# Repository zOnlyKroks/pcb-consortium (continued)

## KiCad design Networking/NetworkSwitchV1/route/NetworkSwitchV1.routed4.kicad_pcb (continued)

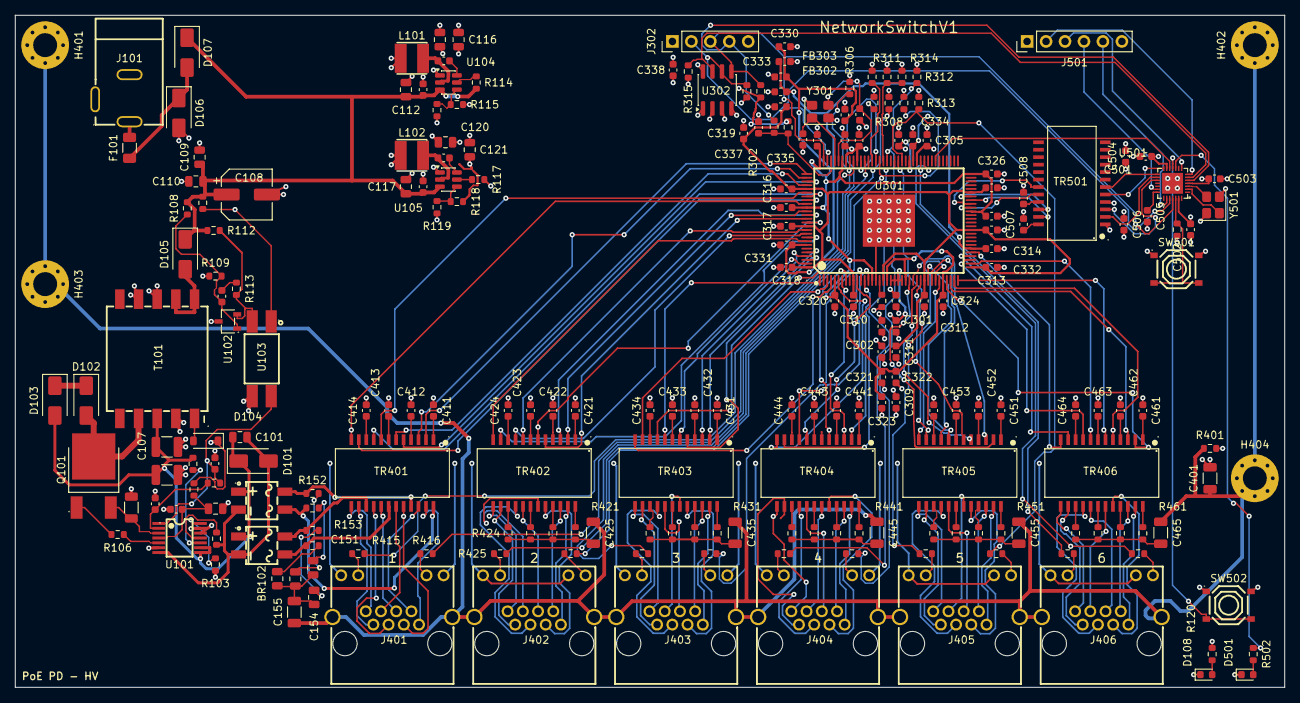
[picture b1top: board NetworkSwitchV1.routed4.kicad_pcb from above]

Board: 4 copper layers, 170.0 x 90.0 mm, 226 parts (0 on the bottom side), 251 nets.

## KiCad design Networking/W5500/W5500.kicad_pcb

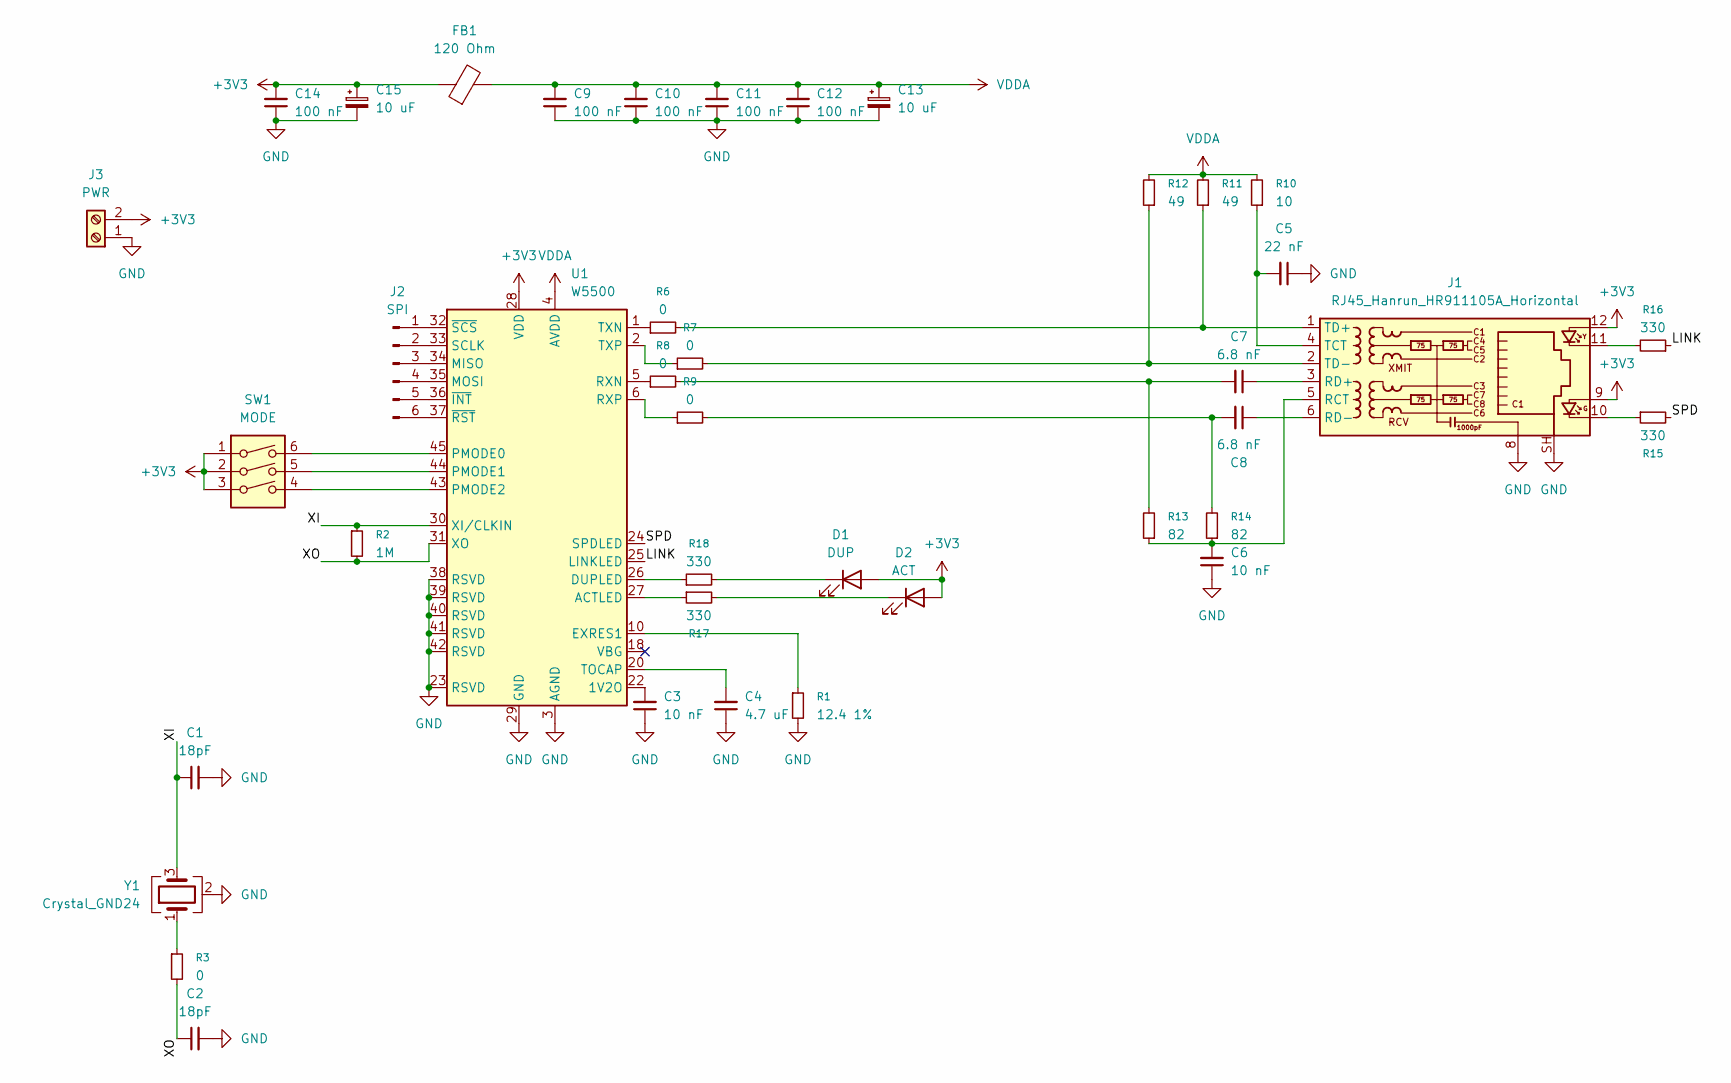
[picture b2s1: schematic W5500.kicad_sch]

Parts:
C1, C2: 18pF; C_0603_1608Metric
C3, C6: 10 nF; C_0603_1608Metric
C4: 4.7 uF; C_0805_2012Metric
C5: 22 nF; C_0603_1608Metric
C7, C8: 6.8 nF; C_0603_1608Metric
C9, C10, C11, C12, C14: 100 nF; C_0603_1608Metric
C13, C15: 10 uF; C_0805_2012Metric
D1: DUP; LED_0603_1608Metric
D2: ACT; LED_0603_1608Metric
FB1: 120 Ohm; R_0603_1608Metric
J1: RJ45_Hanrun_HR911105A_Horizontal
J2: SPI; PinHeader_1x06_P2.54mm_Vertical
J3: PWR; WJ500V-5.08-2P
R1: 12.4 1%; R_0603_1608Metric
R2: 1M; R_0603_1608Metric
R3, R6, R7, R8, R9: 0; R_0603_1608Metric
R10: 10; R_0603_1608Metric
R11, R12: 49; R_0603_1608Metric
R13, R14: 82; R_0603_1608Metric
R15, R16, R17, R18: 330; R_0603_1608Metric
SW1: MODE
U1: W5500; LQFP-48_7x7mm_P0.5mm
Y1: Crystal_GND24; Crystal_SMD_3225-4Pin_3.2x2.5mm

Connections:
+3V3: C14.2, C15.1, D1.2 (A), D2.2 (A), FB1.1, J1.9, J1.12, J3.2, SW1.1, SW1.2, SW1.3, U1.28 (VDD)
/LINK: R16.1, U1.25 (LINKLED)
/SPD: R15.2, U1.24 (SPDLED)
/XI: C1.1, R2.1, U1.30 (XI/CLKIN), Y1.3
/XO: C2.1, R2.2, R3.2, U1.31 (XO)
GND: C1.2, C2.2, C3.1, C4.1, C5.1, C6.1, C9.1, C10.1, C11.1, C12.1, C13.2, C14.1, C15.2, J1.8, J1.SH, J3.1, R1.2, U1.3 (AGND), U1.9 (AGND), U1.14 (AGND), U1.16 (AGND), U1.19 (AGND), U1.23 (RSVD), U1.29 (GND), U1.38 (RSVD), U1.39 (RSVD), U1.40 (RSVD), U1.41 (RSVD), U1.42 (RSVD), U1.48 (AGND), Y1.2 (G), Y1.4 (G)
unnamed: C7.2, R8.2, R13.2
unnamed: C8.2, R9.2, R14.2
unnamed: D1.1 (K), R18.2
unnamed: D2.1 (K), R17.2
unnamed: J1.10, R15.1
unnamed: J1.11, R16.2
unnamed: C6.2, J1.5 (RCT), R13.1, R14.1
unnamed: C7.1, J1.3 (RD+)
unnamed: C8.1, J1.6 (RD-)
unnamed: C5.2, J1.4 (TCT), R10.1
unnamed: J1.1 (TD+), R6.2, R11.1
unnamed: J1.2 (TD-), R7.2, R12.1
unnamed: J2.1, U1.32 (~SCS)
unnamed: J2.2, U1.33 (SCLK)
unnamed: J2.3, U1.34 (MISO)
unnamed: J2.4, U1.35 (MOSI)
unnamed: J2.5, U1.36 (~INT)
unnamed: J2.6, U1.37 (~RST)
unnamed: R3.1, Y1.1
unnamed: C3.2, U1.22 (1V2O)
unnamed: R17.1, U1.27 (ACTLED)
unnamed: R18.1, U1.26 (DUPLED)
unnamed: R1.1, U1.10 (EXRES1)
unnamed: SW1.6, U1.45 (PMODE0)
unnamed: SW1.5, U1.44 (PMODE1)
unnamed: SW1.4, U1.43 (PMODE2)
unnamed: R8.1, U1.5 (RXN)
unnamed: R9.1, U1.6 (RXP)
unnamed: C4.2, U1.20 (TOCAP)
unnamed: R6.1, U1.1 (TXN)
unnamed: R7.1, U1.2 (TXP)
VDDA: C9.2, C10.2, C11.2, C12.2, C13.1, FB1.2, R10.2, R11.2, R12.2, U1.4 (AVDD), U1.8 (AVDD), U1.11 (AVDD), U1.15 (AVDD), U1.17 (AVDD), U1.21 (AVDD)

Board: 2 copper layers, 39 parts (0 on the bottom side), 35 nets, no tracks yet.

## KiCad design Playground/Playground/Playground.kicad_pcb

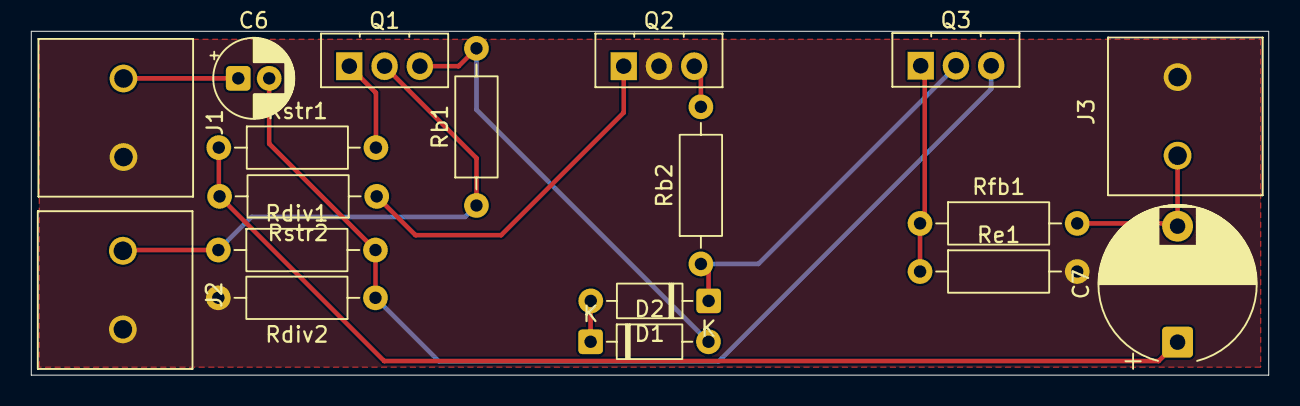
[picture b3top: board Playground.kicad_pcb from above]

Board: 2 copper layers, 80.0 x 22.2 mm, 18 parts (0 on the bottom side), 13 nets.

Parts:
C6: 1 uF; CP_Radial_D5.0mm_P2.00mm
C7: 1000 uF; CP_Radial_D10.0mm_P7.50mm
D1, D2: 1N4148; D_DO-35_SOD27_P7.62mm_Horizontal
J1, J2: Vin; WJ500V-5.08-2P
J3: Out; WJ500V-5.08-2P
Q1, Q3: BD139; TO-126-3_Vertical
Q2: BD140; TO-126-3_Vertical
Rb1: 1k; R_Axial_DIN0207_L6.3mm_D2.5mm_P10.16mm_Horizontal
Rb2: 68; R_Axial_DIN0207_L6.3mm_D2.5mm_P10.16mm_Horizontal
Rdiv1: 100k; R_Axial_DIN0207_L6.3mm_D2.5mm_P10.16mm_Horizontal
Rdiv2: 15k; R_Axial_DIN0207_L6.3mm_D2.5mm_P10.16mm_Horizontal
Re1: 100; R_Axial_DIN0207_L6.3mm_D2.5mm_P10.16mm_Horizontal
Rfb1: 3.3k; R_Axial_DIN0207_L6.3mm_D2.5mm_P10.16mm_Horizontal
Rstr1, Rstr2: 2.2; R_Axial_DIN0207_L6.3mm_D2.5mm_P10.16mm_Horizontal

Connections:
/IN: C6.1, J1.1
/OUT: C7.2, J3.1, Rfb1.2
GND: J1.2, J2.2, J3.2, Q2.2 (C), Rdiv2.2, Re1.2
unnamed: C7.1, Rstr1.1, Rstr2.2
unnamed: D1.2 (A), D2.1 (K)
unnamed: D1.1 (K), Q3.2 (C), Rb2.1
unnamed: D2.2 (A), Q1.3 (B), Rb1.2
unnamed: J2.1, Q1.2 (C), Rb1.1, Rdiv1.1
unnamed: Q1.1 (E), Rstr1.2
unnamed: Q2.3 (B), Rb2.2
unnamed: Q2.1 (E), Rstr2.1
unnamed: C6.2, Q3.3 (B), Rdiv1.2, Rdiv2.1
unnamed: Q3.1 (E), Re1.1, Rfb1.1

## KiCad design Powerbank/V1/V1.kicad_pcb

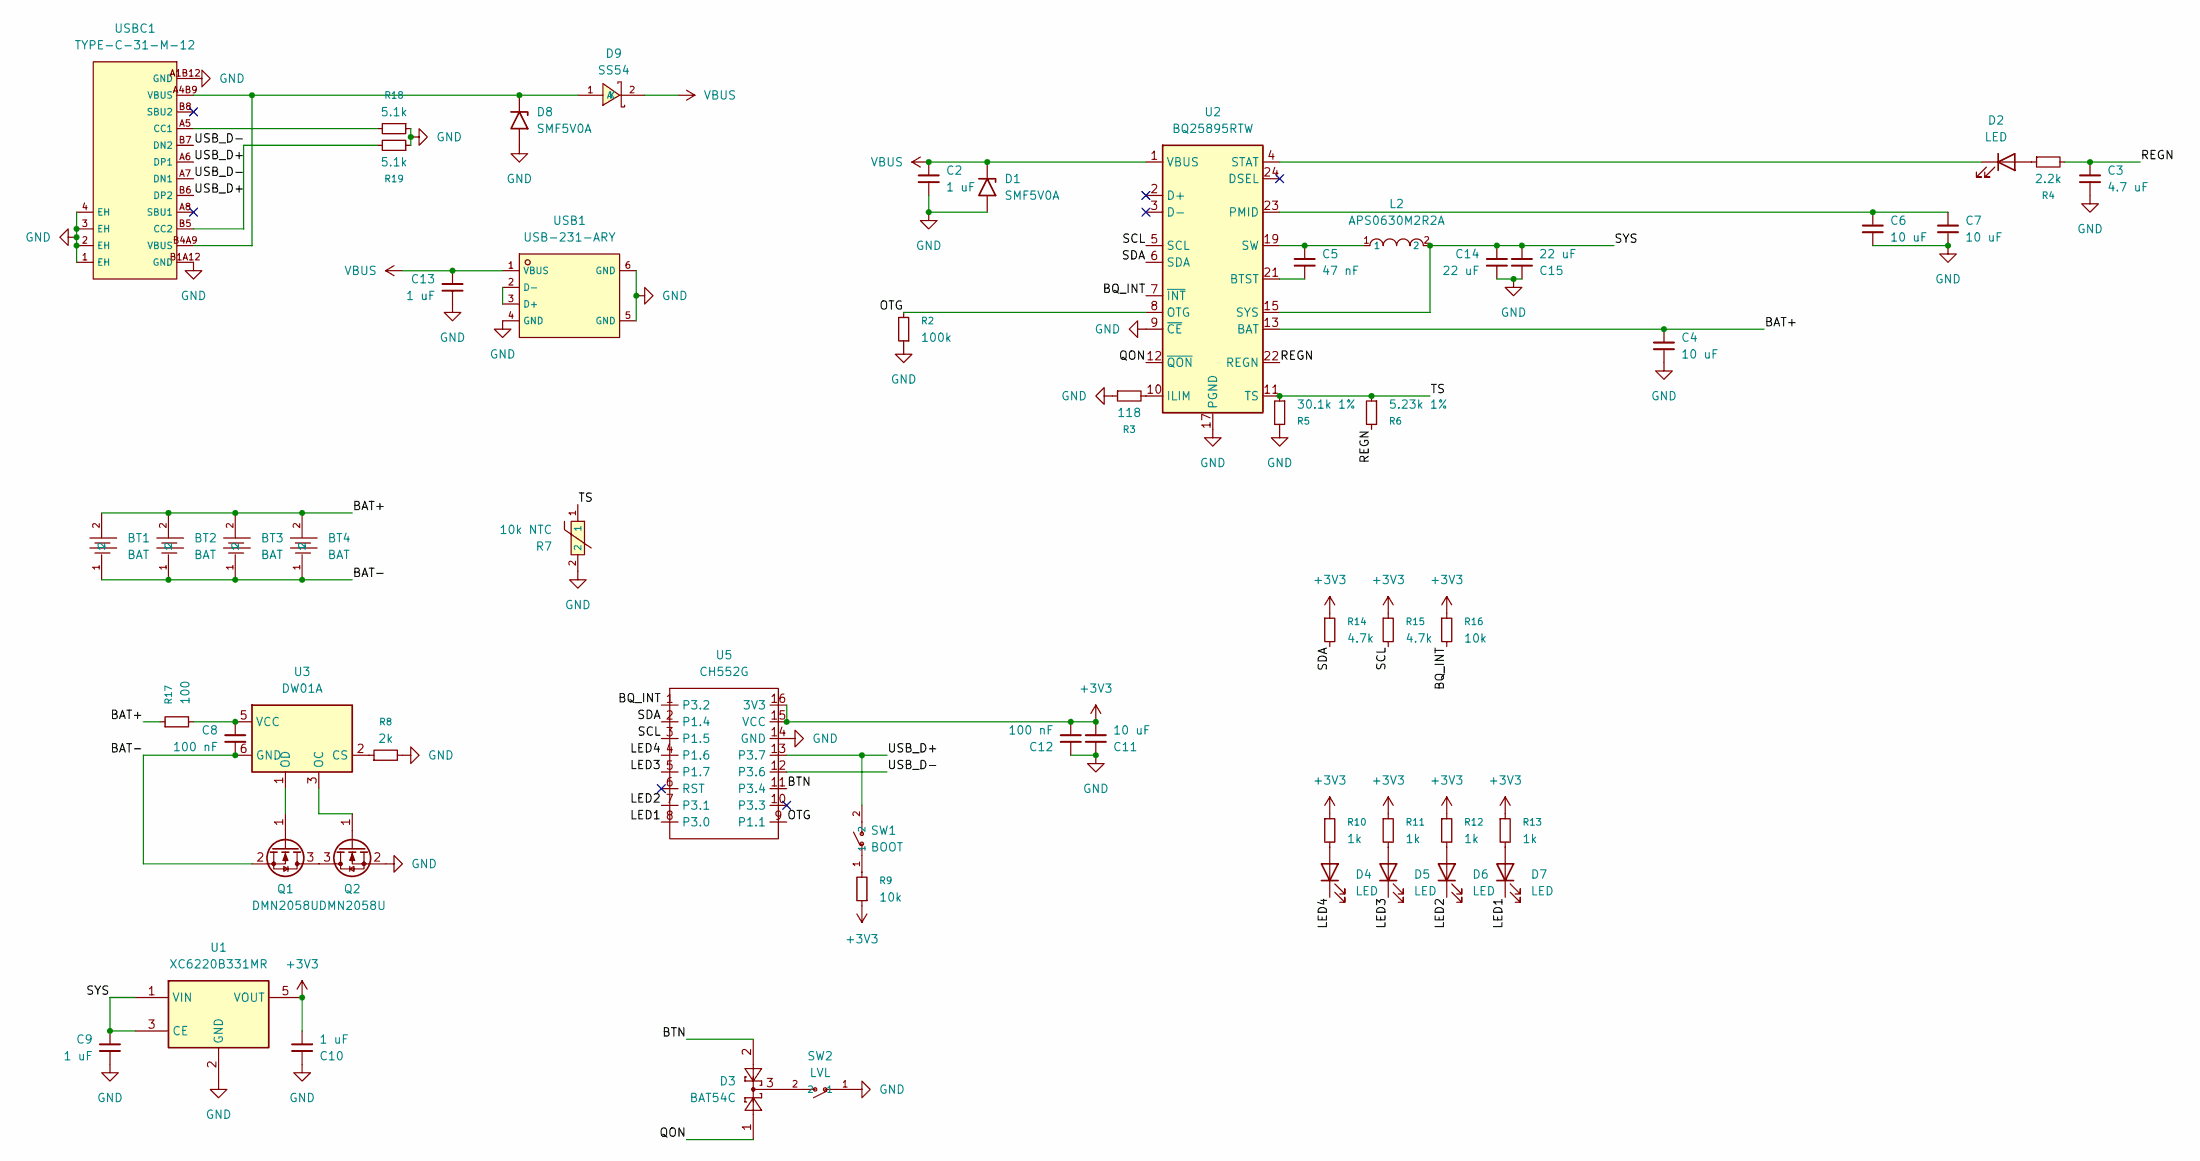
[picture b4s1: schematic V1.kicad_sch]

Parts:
BT1, BT2, BT3, BT4: BAT; C2988620_BATTERY-SMD_18650-1S-L77_1-W20_7-1; LCSC C2988620
C2, C9, C10, C13: 1 uF; C_0805_2012Metric
C3: 4.7 uF; C_0805_2012Metric
C4, C6, C7, C11: 10 uF; C_0805_2012Metric
C5: 47 nF; C_0805_2012Metric
C8, C12: 100 nF; C_0805_2012Metric
C14, C15: 22 uF; C_0805_2012Metric
D1, D8: SMF5V0A; D_SMF
D2, D4, D5, D6, D7: LED; C2892549_R0805
D3: BAT54C; SOT-23
D9: SS54; C22452_SMA_L4_4-W2_8-LS5_4-R-RD; LCSC C22452
L2: APS0630M2R2A; C47327201_IND-SMD_L7_7-W6_6_APS0630; LCSC C47327201
Q1, Q2: DMN2058U; SOT-23
R2: 100k; R_0805_2012Metric
R3: 118; R_0805_2012Metric
R4: 2.2k; R_0805_2012Metric
R5: 30.1k 1%; R_0805_2012Metric
R6: 5.23k 1%; R_0805_2012Metric
R7: 10k NTC; C2892549_R0805; LCSC C2892549
R8: 2k; R_0805_2012Metric
R9, R16: 10k; R_0805_2012Metric
R10, R11, R12, R13: 1k; R_0805_2012Metric
R14, R15: 4.7k; R_0805_2012Metric
R17: 100; R_0805_2012Metric
R18, R19: 5.1k; R_0805_2012Metric
SW1: BOOT; C54407262_SW-SMD_L4_0-W3_0-LS5_0; LCSC C54407262
SW2: LVL; C54407262_SW-SMD_L4_0-W3_0-LS5_0; LCSC C54407262
U1: XC6220B331MR; SOT-23-5
U2: BQ25895RTW; Texas_RTW_WQFN-24-1EP_4x4mm_P0.5mm_EP2.7x2.7mm_ThermalVias
U3: DW01A; SOT-23-6
U5: CH552G
USB1: USB-231-ARY; C720525_USB-A-TH_USB-231-ARY; LCSC C720525
USBC1: TYPE-C-31-M-12; C165948_USB-C_SMD-TYPE-C-31-M-12_1; LCSC C165948

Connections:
+3V3: C10.1, C11.1, C12.1, R9.1, R10.1, R11.1, R12.1, R13.1, R14.1, R15.1, R16.1, U1.5 (VOUT), U5.15 (VCC), U5.16 (3V3)
/BAT+: BT1.2, BT2.2, BT3.2, BT4.2, C4.2, R17.1, U2.13 (BAT), U2.14 (BAT)
/BAT-: BT1.1, BT2.1, BT3.1, BT4.1, C8.1, Q1.2 (S), U3.6 (GND)
/BQ_INT: R16.2, U2.7 (~INT), U5.1 (P3.2)
/BTN: D3.2, U5.11 (P3.4)
/LED1: D7.1 (K), U5.8 (P3.0)
/LED2: D6.1 (K), U5.7 (P3.1)
/LED3: D5.1 (K), U5.5 (P1.7)
/LED4: D4.1 (K), U5.4 (P1.6)
/OTG: R2.2, U2.8 (OTG), U5.9 (P1.1)
/QON: D3.1, U2.12 (~QON)
/REGN: C3.2, R4.2, R6.2, U2.22 (REGN)
/SCL: R15.2, U2.5 (SCL), U5.3 (P1.5)
/SDA: R14.2, U2.6 (SDA), U5.2 (P1.4)
/SYS: C9.2, C14.2, C15.1, L2.2, U1.1 (VIN), U1.3 (CE), U2.15 (SYS), U2.16 (SYS)
/TS: R5.1, R6.1, R7.1, U2.11 (TS)
/USB_D+: SW1.2, U5.13 (P3.7), USBC1.A6 (DP1), USBC1.B6 (DP2)
/USB_D-: U5.12 (P3.6), USBC1.A7 (DN1), USBC1.B7 (DN2)
GND: C2.1, C3.1, C4.1, C6.1, C7.1, C9.1, C10.2, C11.2, C12.2, C13.1, C14.1, C15.2, D1.2 (A2), D8.2 (A2), Q2.2 (S), R2.1, R3.1, R5.2, R7.2, R8.2, R18.1, R19.1, SW2.1, U1.2 (GND), U2.9 (~CE), U2.17 (PGND), U2.18 (PGND), U2.25 (PGND), U5.14 (GND), USB1.4 (GND), USB1.5 (GND), USB1.6 (GND), USBC1.1 (EH), USBC1.2 (EH), USBC1.3 (EH), USBC1.4 (EH), USBC1.A1B12 (GND), USBC1.B1A12 (GND)
unnamed: C5.2, L2.1, U2.19 (SW), U2.20 (SW)
unnamed: D2.2 (A), R4.1
unnamed: D2.1 (K), U2.4 (STAT)
unnamed: D3.3, SW2.2
unnamed: D4.2 (A), R10.2
unnamed: D5.2 (A), R11.2
unnamed: D6.2 (A), R12.2
unnamed: D7.2 (A), R13.2
unnamed: D8.1 (A1), D9.1 (A), USBC1.A4B9 (VBUS), USBC1.B4A9 (VBUS)
unnamed: Q1.3 (D), Q2.3 (D)
unnamed: Q1.1 (G), U3.1 (OD)
unnamed: Q2.1 (G), U3.3 (OC)
unnamed: R9.2, SW1.1
unnamed: C5.1, U2.21 (BTST)
unnamed: R3.2, U2.10 (ILIM)
unnamed: C6.2, C7.2, U2.23 (PMID)
unnamed: R8.1, U3.2 (CS)
unnamed: C8.2, R17.2, U3.5 (VCC)
unnamed: USB1.2 (D-), USB1.3 (D+)
unnamed: R18.2, USBC1.A5 (CC1)
unnamed: R19.2, USBC1.B5 (CC2)
VBUS: C2.2, C13.2, D1.1 (A1), D9.2 (K), U2.1 (VBUS), USB1.1 (VBUS)

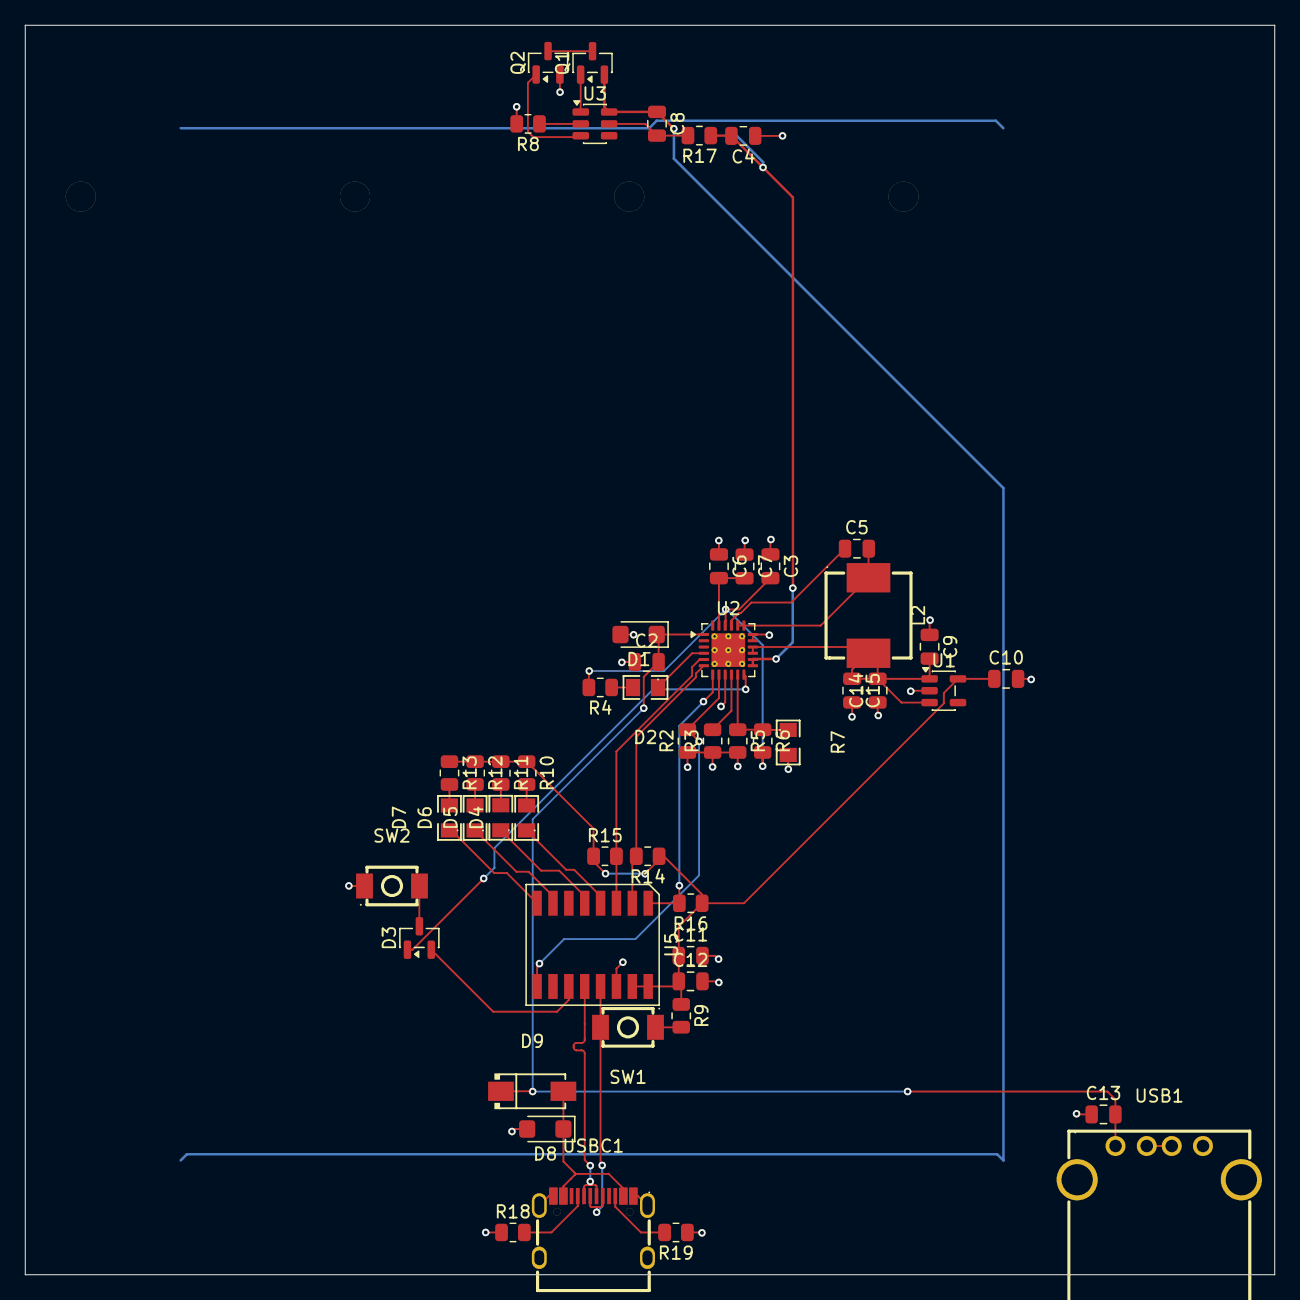
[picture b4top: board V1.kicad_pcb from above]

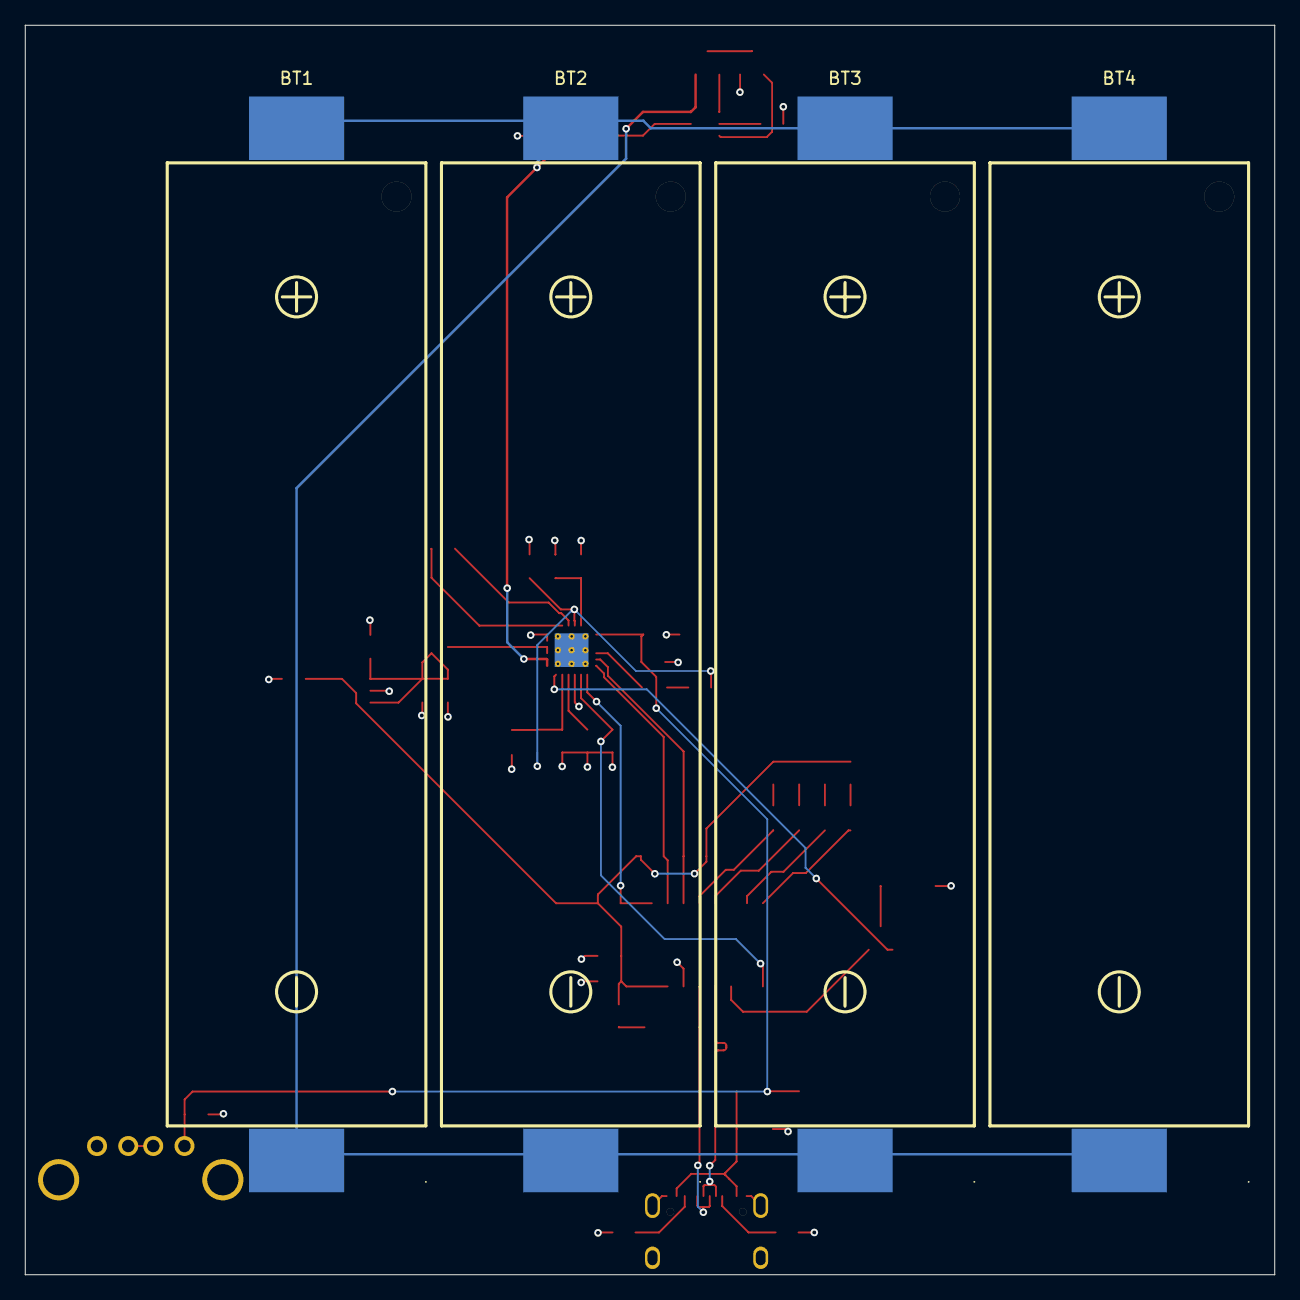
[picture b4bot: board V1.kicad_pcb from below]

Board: 4 copper layers, 100.0 x 100.0 mm, 56 parts (4 on the bottom side), 41 nets.

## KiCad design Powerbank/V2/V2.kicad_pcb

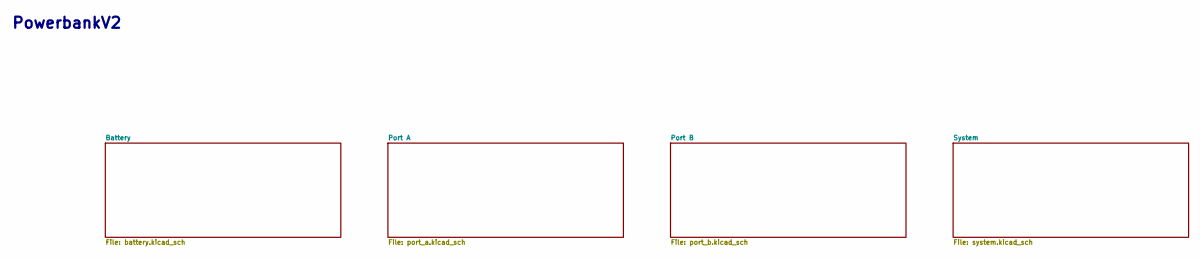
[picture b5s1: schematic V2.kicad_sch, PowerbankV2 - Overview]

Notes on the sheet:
PowerbankV2

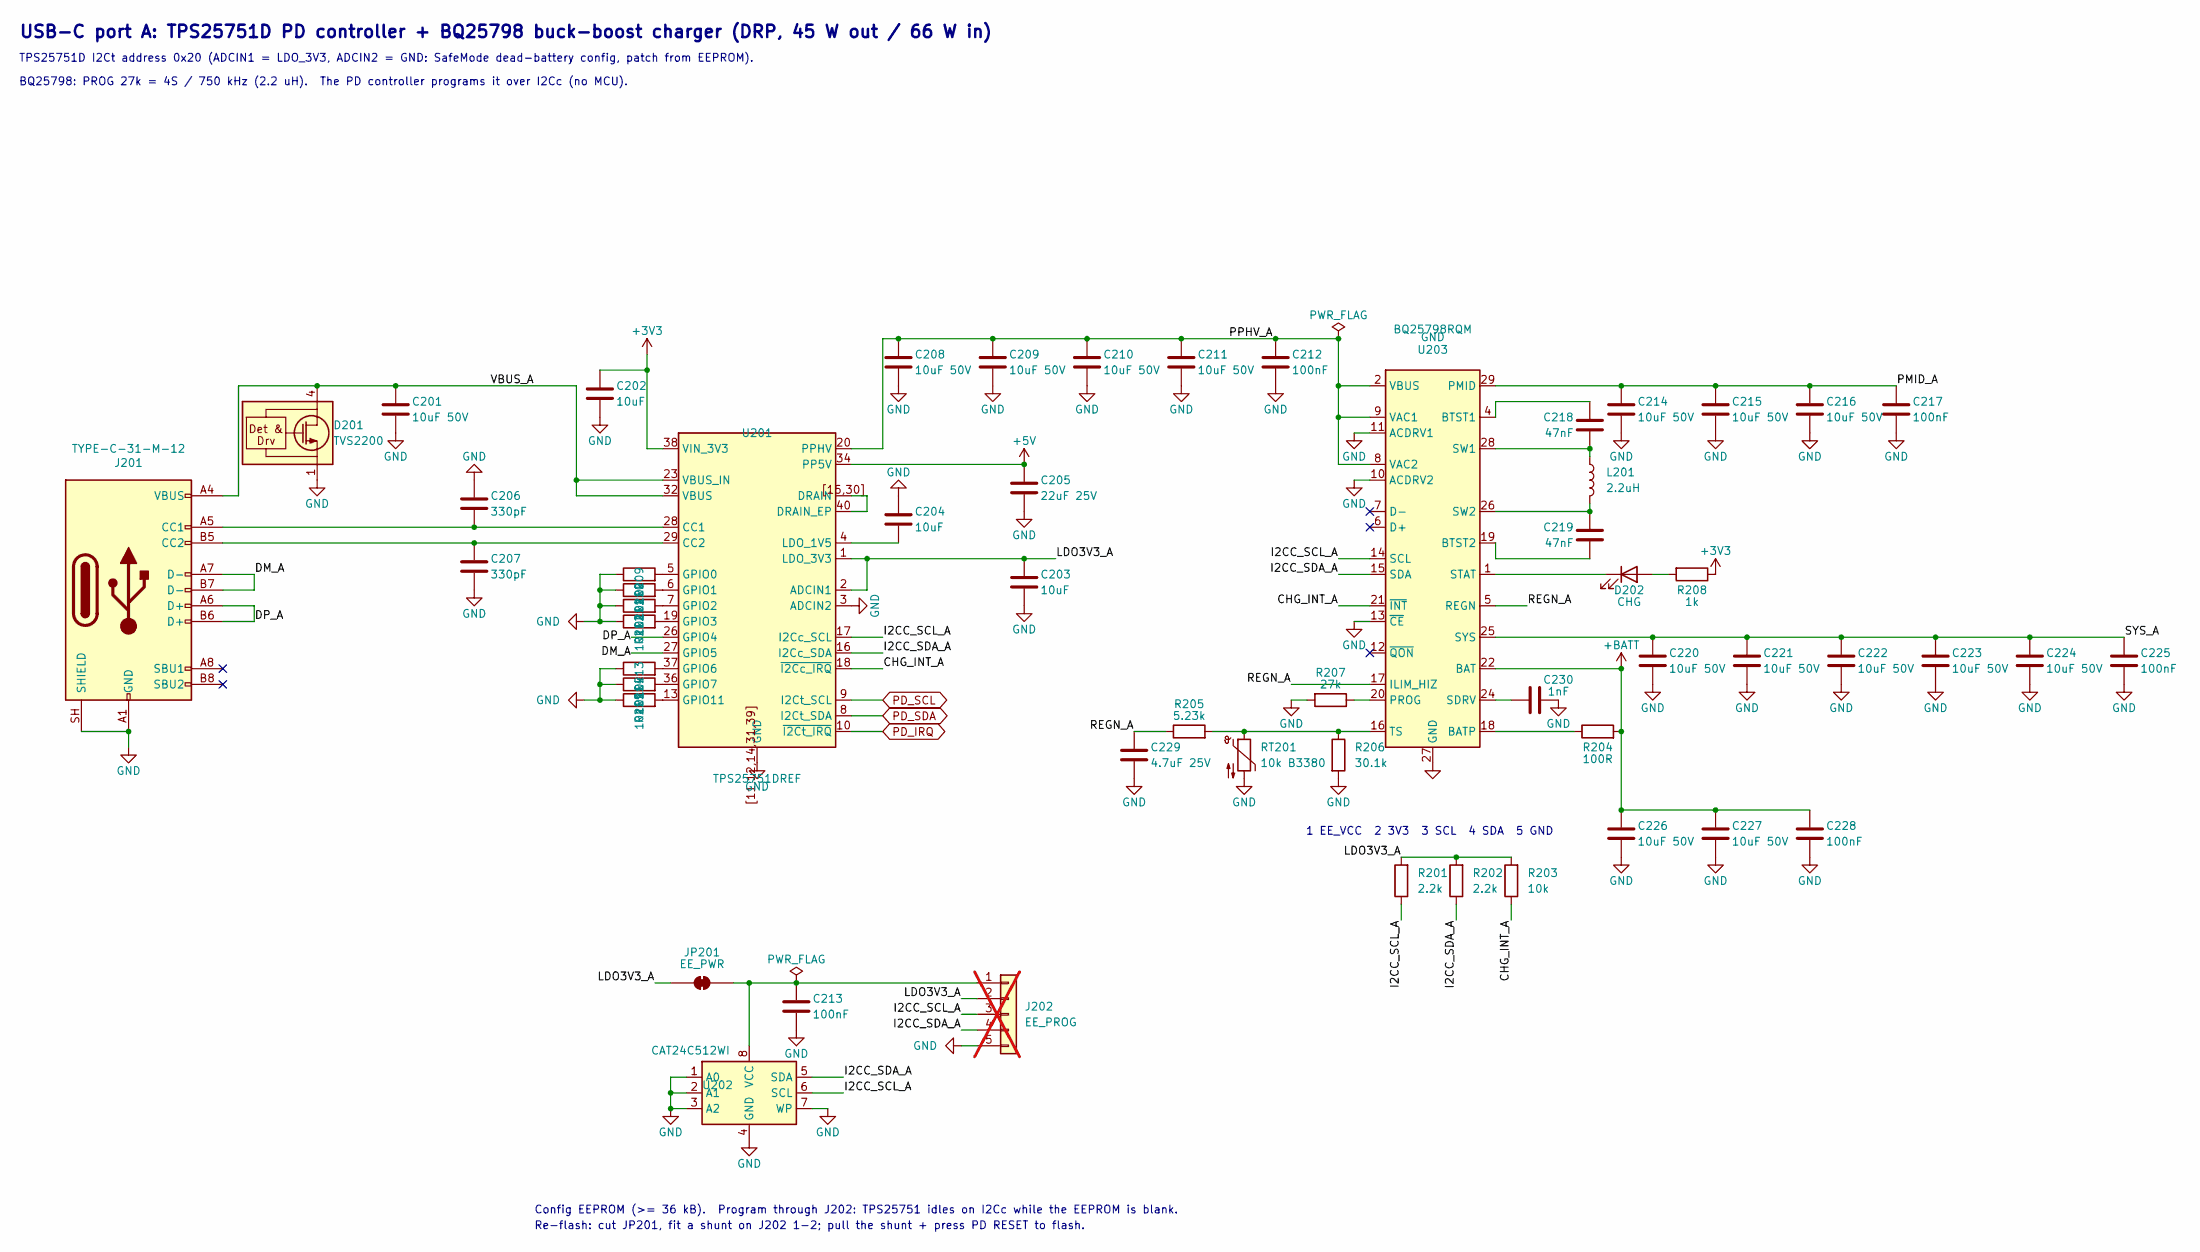
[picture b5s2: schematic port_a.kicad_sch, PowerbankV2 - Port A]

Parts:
C201, C208, C209, C210, C211, C214, C215, C216, C220, C221, C222, C223, C224, C226, C227: 10uF 50V; C_1206_3216Metric; LCSC Part # C13585
C202, C203, C204: 10uF; C_0603_1608Metric; LCSC Part # C19702
C205: 22uF 25V; C_0805_2012Metric; LCSC Part # C45783
C206, C207: 330pF; C_0603_1608Metric; LCSC Part # C1664
C212, C213, C217, C225, C228: 100nF; C_0603_1608Metric; LCSC Part # C14663
C218, C219: 47nF; C_0603_1608Metric; LCSC Part # C1622
C229: 4.7uF 25V; C_0805_2012Metric; LCSC Part # C1779
C230: 1nF; C_0603_1608Metric; LCSC Part # C1588
D201: TVS2200; WSON-6-1EP_2x2mm_P0.65mm_EP1x1.6mm; LCSC Part # C523793
D202: CHG; LED_0603_1608Metric; LCSC Part # C2286
J201: TYPE-C-31-M-12; USB_C_Receptacle_HRO_TYPE-C-31-M-12; LCSC Part # C165948
J202: EE_PROG; PinHeader_1x05_P2.54mm_Vertical; not fitted
JP201: EE_PWR; SolderJumper-2_P1.3mm_Bridged_RoundedPad1.0x1.5mm
L201: 2.2uH; L_7.0x6.6_MWSA0603S; LCSC Part # C408445
R201, R202: 2.2k; R_0603_1608Metric; LCSC Part # C4190
R203, R209, R210, R211, R212, R213, R214, R215: 10k; R_0603_1608Metric; LCSC Part # C25804
R204: 100R; R_0603_1608Metric; LCSC Part # C22775
R205: 5.23k; R_0603_1608Metric; LCSC Part # C23068
R206: 30.1k; R_0603_1608Metric; LCSC Part # C23000
R207: 27k; R_0603_1608Metric; LCSC Part # C22967
R208: 1k; R_0603_1608Metric; LCSC Part # C21190
RT201: 10k B3380; R_0603_1608Metric; LCSC Part # C13564
U201: TPS25751DREF; Texas_REF0038A_WQFN-38-2EP_6x4mm_P0.4_Via0.3; LCSC Part # C30169739
U202: CAT24C512WI; SOIC-8_3.9x4.9mm_P1.27mm; LCSC Part # C79986
U203: BQ25798RQM; Texas_RQM0029A_VQFN-29_4x4mm_P0.4mm; LCSC Part # C2876593

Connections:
+3V3: C202.1, R208.1, U201.38 (VIN_3V3); also elsewhere on the board
+5V: C205.1, U201.34 (PP5V); also elsewhere on the board
+BATT: C226.1, C227.1, C228.1, R204.2, U203.22 (BAT), U203.23 (BAT); also elsewhere on the board
/Port A/CHG_INT_A: R203.1, U201.18 (~I2Cc_IRQ), U203.21 (~INT)
/Port A/DM_A: J201.A7 (D-), J201.B7 (D-), U201.27 (GPIO5)
/Port A/DP_A: J201.A6 (D+), J201.B6 (D+), U201.26 (GPIO4)
/Port A/I2CC_SCL_A: J202.3, R201.1, U201.17 (I2Cc_SCL), U202.6 (SCL), U203.14 (SCL)
/Port A/I2CC_SDA_A: J202.4, R202.1, U201.16 (I2Cc_SDA), U202.5 (SDA), U203.15 (SDA)
/Port A/LDO3V3_A: C203.1, J202.2, JP201.1 (A), R201.2, R202.2, R203.2, U201.1 (LDO_3V3), U201.2 (ADCIN1)
/Port A/PMID_A: C214.1, C215.1, C216.1, C217.1, U203.29 (PMID)
/Port A/PPHV_A: C208.1, C209.1, C210.1, C211.1, C212.1, U201.20 (PPHV), U203.2 (VBUS), U203.3 (VBUS), U203.8 (VAC2), U203.9 (VAC1)
/Port A/REGN_A: C229.1, R205.1, U203.5 (REGN), U203.17 (ILIM_HIZ)
/Port A/SYS_A: C220.1, C221.1, C222.1, C223.1, C224.1, C225.1, U203.25 (SYS)
/Port A/VBUS_A: C201.1, D201.4 (IN), D201.5 (IN), D201.6 (IN), J201.A4 (VBUS), J201.A9 (VBUS), J201.B4 (VBUS), J201.B9 (VBUS), U201.23 (VBUS_IN), U201.32 (VBUS)
GND: C201.2, C202.2, C203.2, C204.2, C205.2, C206.2, C207.2, C208.2, C209.2, C210.2, C211.2, C212.2, C213.2, C214.2, C215.2, C216.2, C217.2, C220.2, C221.2, C222.2, C223.2, C224.2, C225.2, C226.2, C227.2, C228.2, C229.2, C230.2, D201.1 (GND), D201.2 (GND), D201.3 (GND), D201.7 (GND), J201.A1 (GND), J201.A12 (GND), J201.B1 (GND), J201.B12 (GND), J201.SH (SHIELD), J202.5, R206.2, R207.2, R209.1, R210.1, R211.1, R212.1, R213.1, R214.1, R215.1, RT201.2, U201.3 (ADCIN2), U201.11, U201.12, U201.14, U201.31, U201.39, U201.[11,12,14,31,39] (GND), U202.1 (A0), U202.2 (A1), U202.3 (A2), U202.4 (GND), U202.7 (WP), U203.10 (ACDRV2), U203.11 (ACDRV1), U203.13 (~CE), U203.27 (GND); also elsewhere on the board
unnamed: D202.2 (A), R208.2
unnamed: D202.1 (K), U203.1 (STAT)
unnamed: C206.1, J201.A5 (CC1), U201.28 (CC1)
unnamed: C207.1, J201.B5 (CC2), U201.29 (CC2)
unnamed: C213.1, J202.1, JP201.2 (B), U202.8 (VCC)
unnamed: U201.15, U201.30, U201.40 (DRAIN_EP), U201.[15,30] (DRAIN)
unnamed: R209.2, U201.5 (GPIO0)
unnamed: R210.2, U201.6 (GPIO1)
unnamed: R211.2, U201.7 (GPIO2)
unnamed: R212.2, U201.19 (GPIO3)
unnamed: R213.2, U201.37 (GPIO6)
unnamed: R214.2, U201.36 (GPIO7)
unnamed: R215.2, U201.13 (GPIO11)
unnamed: C204.1, U201.4 (LDO_1V5)
unnamed: R204.1, U203.18 (BATP)
unnamed: C218.1, U203.4 (BTST1)
unnamed: C219.1, U203.19 (BTST2)
unnamed: R207.1, U203.20 (PROG)
unnamed: C230.1, U203.24 (SDRV)
unnamed: C218.2, L201.1, U203.28 (SW1)
unnamed: C219.2, L201.2, U203.26 (SW2)
unnamed: R205.2, R206.1, RT201.1, U203.16 (TS)
PD_IRQ: U201.10 (~I2Ct_IRQ); also elsewhere on the board
PD_SCL: U201.9 (I2Ct_SCL); also elsewhere on the board
PD_SDA: U201.8 (I2Ct_SDA); also elsewhere on the board

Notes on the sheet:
TPS25751D I2Ct address 0x20 (ADCIN1 = LDO_3V3, ADCIN2 = GND: SafeMode dead-battery config, patch from EEPROM).
Config EEPROM (>= 36 kB). Program through J202: TPS25751 idles on I2Cc while the EEPROM is blank.
1 EE_VCC 2 3V3 3 SCL 4 SDA 5 GND
USB-C port A: TPS25751D PD controller + BQ25798 buck-boost charger (DRP, 45 W out / 66 W in)
Re-flash: cut JP201, fit a shunt on J202 1-2; pull the shunt + press PD RESET to flash.
BQ25798: PROG 27k = 4S / 750 kHz (2.2 uH). The PD controller programs it over I2Cc (no MCU).
